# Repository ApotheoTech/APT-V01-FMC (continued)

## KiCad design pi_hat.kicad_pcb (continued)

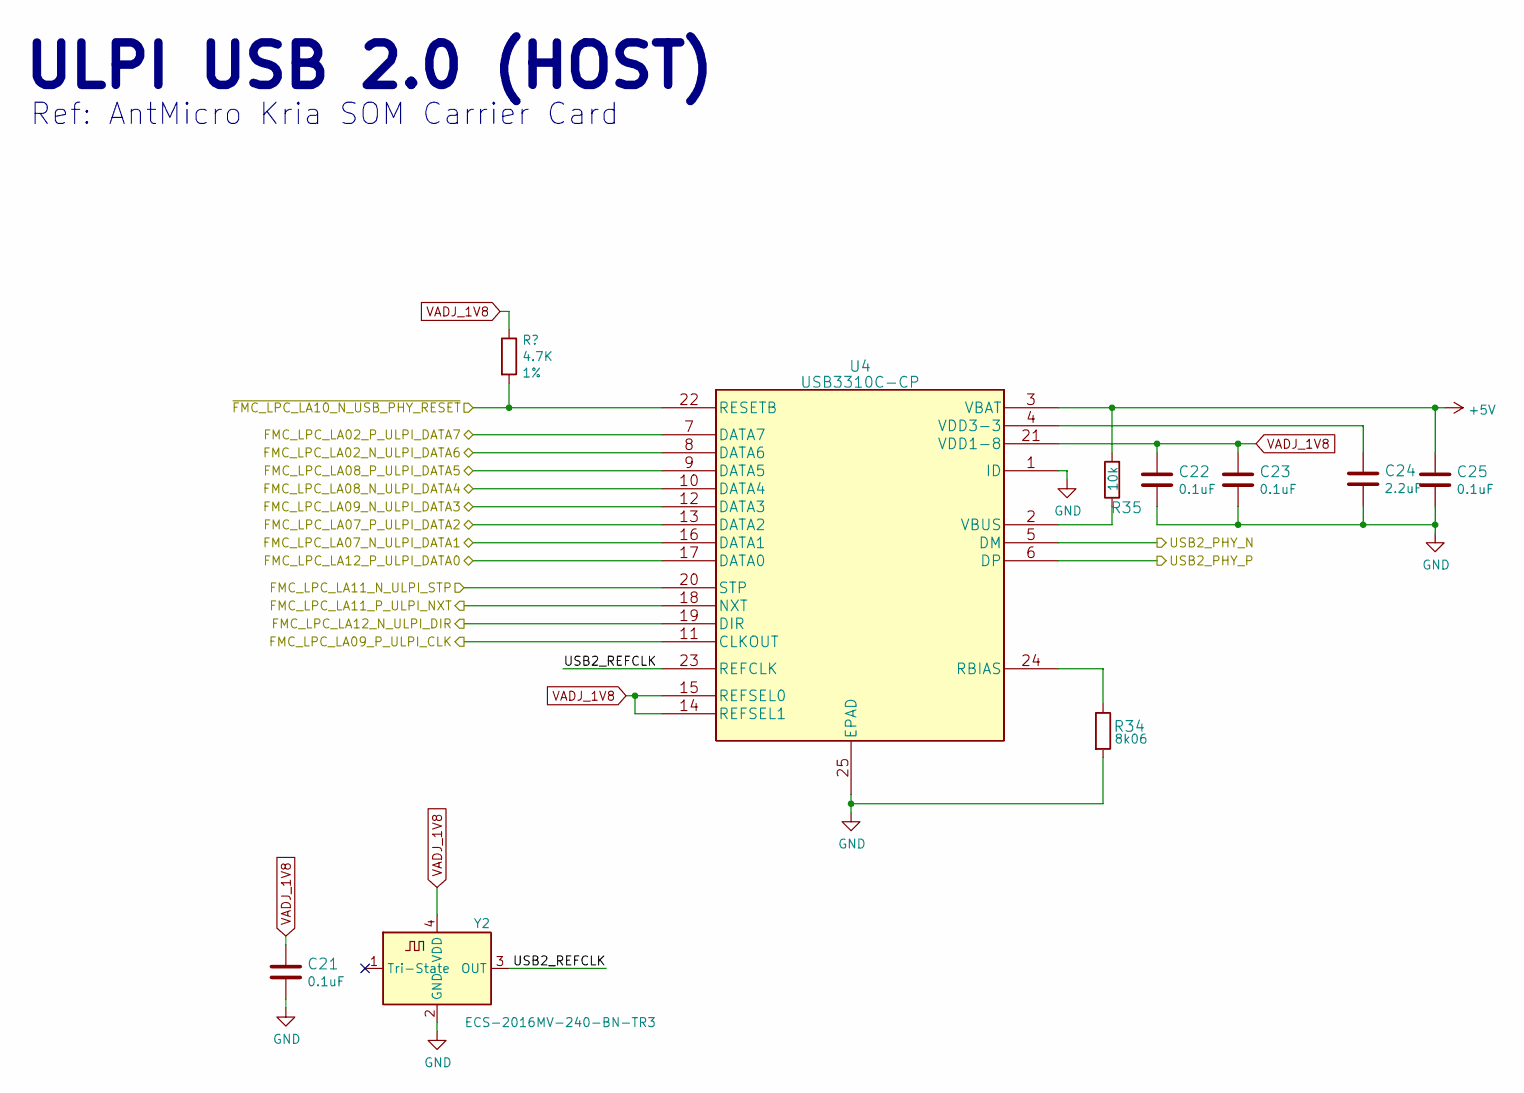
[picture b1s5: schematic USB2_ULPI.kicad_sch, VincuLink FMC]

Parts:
C21, C22, C23, C25: 0.1uF; C_0402_1005Metric; MPN GRM155R61H104KE14D
C24: C_2u2_0402; C_0402_1005Metric; PartNumber C1005X5R1A225K050BC
R33: 4.7K; R_0402_1005Metric; Tolerance 1%; PartNumber CRCW04024K70FKED
R34: 8.06k; R_0402_1005Metric; PartNumber CRCW04028K06FKEDC
R35: R_10k_0402; R_0402_1005Metric; PartNumber CRCW040210K0FKEDHP
U4: USB3310C-CP; Microchip_QFN24_4X4; MPN USB3310C-CP
Y2: ECS-2016MV-240-BN-TR3; ECS-2016MV; MPN ECS-2016MV-240-BN-TR3

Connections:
+5V: C25.1, R35.2, U4.3 (VBAT); also elsewhere on the board
/FMC_Conn/FMC_LPC_LA02_N_ULPI_DATA6: U4.8 (DATA6); also elsewhere on the board
/FMC_Conn/FMC_LPC_LA02_P_ULPI_DATA7: U4.7 (DATA7); also elsewhere on the board
/FMC_Conn/FMC_LPC_LA07_N_ULPI_DATA1: U4.16 (DATA1); also elsewhere on the board
/FMC_Conn/FMC_LPC_LA07_P_ULPI_DATA2: U4.13 (DATA2); also elsewhere on the board
/FMC_Conn/FMC_LPC_LA08_N_ULPI_DATA4: U4.10 (DATA4); also elsewhere on the board
/FMC_Conn/FMC_LPC_LA08_P_ULPI_DATA5: U4.9 (DATA5); also elsewhere on the board
/FMC_Conn/FMC_LPC_LA09_N_ULPI_DATA3: U4.12 (DATA3); also elsewhere on the board
/FMC_Conn/FMC_LPC_LA09_P_ULPI_CLK: U4.11 (CLKOUT); also elsewhere on the board
/FMC_Conn/FMC_LPC_LA11_N_ULPI_STP: U4.20 (STP); also elsewhere on the board
/FMC_Conn/FMC_LPC_LA11_P_ULPI_NXT: U4.18 (NXT); also elsewhere on the board
/FMC_Conn/FMC_LPC_LA12_N_ULPI_DIR: U4.19 (DIR); also elsewhere on the board
/FMC_Conn/FMC_LPC_LA12_P_ULPI_DATA0: U4.17 (DATA0); also elsewhere on the board
/FMC_Conn/~FMC_LPC_LA10_N_USB_PHY_RESET: R33.2, U4.22 (RESETB); also elsewhere on the board
/M_2_KeyE/USB2_PHY_N: U4.5 (DM); also elsewhere on the board
/M_2_KeyE/USB2_PHY_P: U4.6 (DP); also elsewhere on the board
/USB_2_ULPI/USB2_REFCLK: U4.23 (REFCLK), Y2.3 (OUT)
GND: C21.2, C22.2, C23.2, C24.2, C25.2, R34.2, U4.1 (ID), U4.25 (EPAD), Y2.2 (GND); also elsewhere on the board
unnamed: R34.1, U4.24 (RBIAS)
unnamed: R35.1, U4.2 (VBUS)
unnamed: C24.1, U4.4 (VDD3-3)
VADJ_1V8: C21.1, C22.1, C23.1, R33.1, U4.14 (REFSEL1), U4.15 (REFSEL0), U4.21 (VDD1-8), Y2.4 (VDD); also elsewhere on the board

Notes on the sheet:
Ref: AntMicro Kria SOM Carrier Card
ULPI USB 2.0 (HOST)

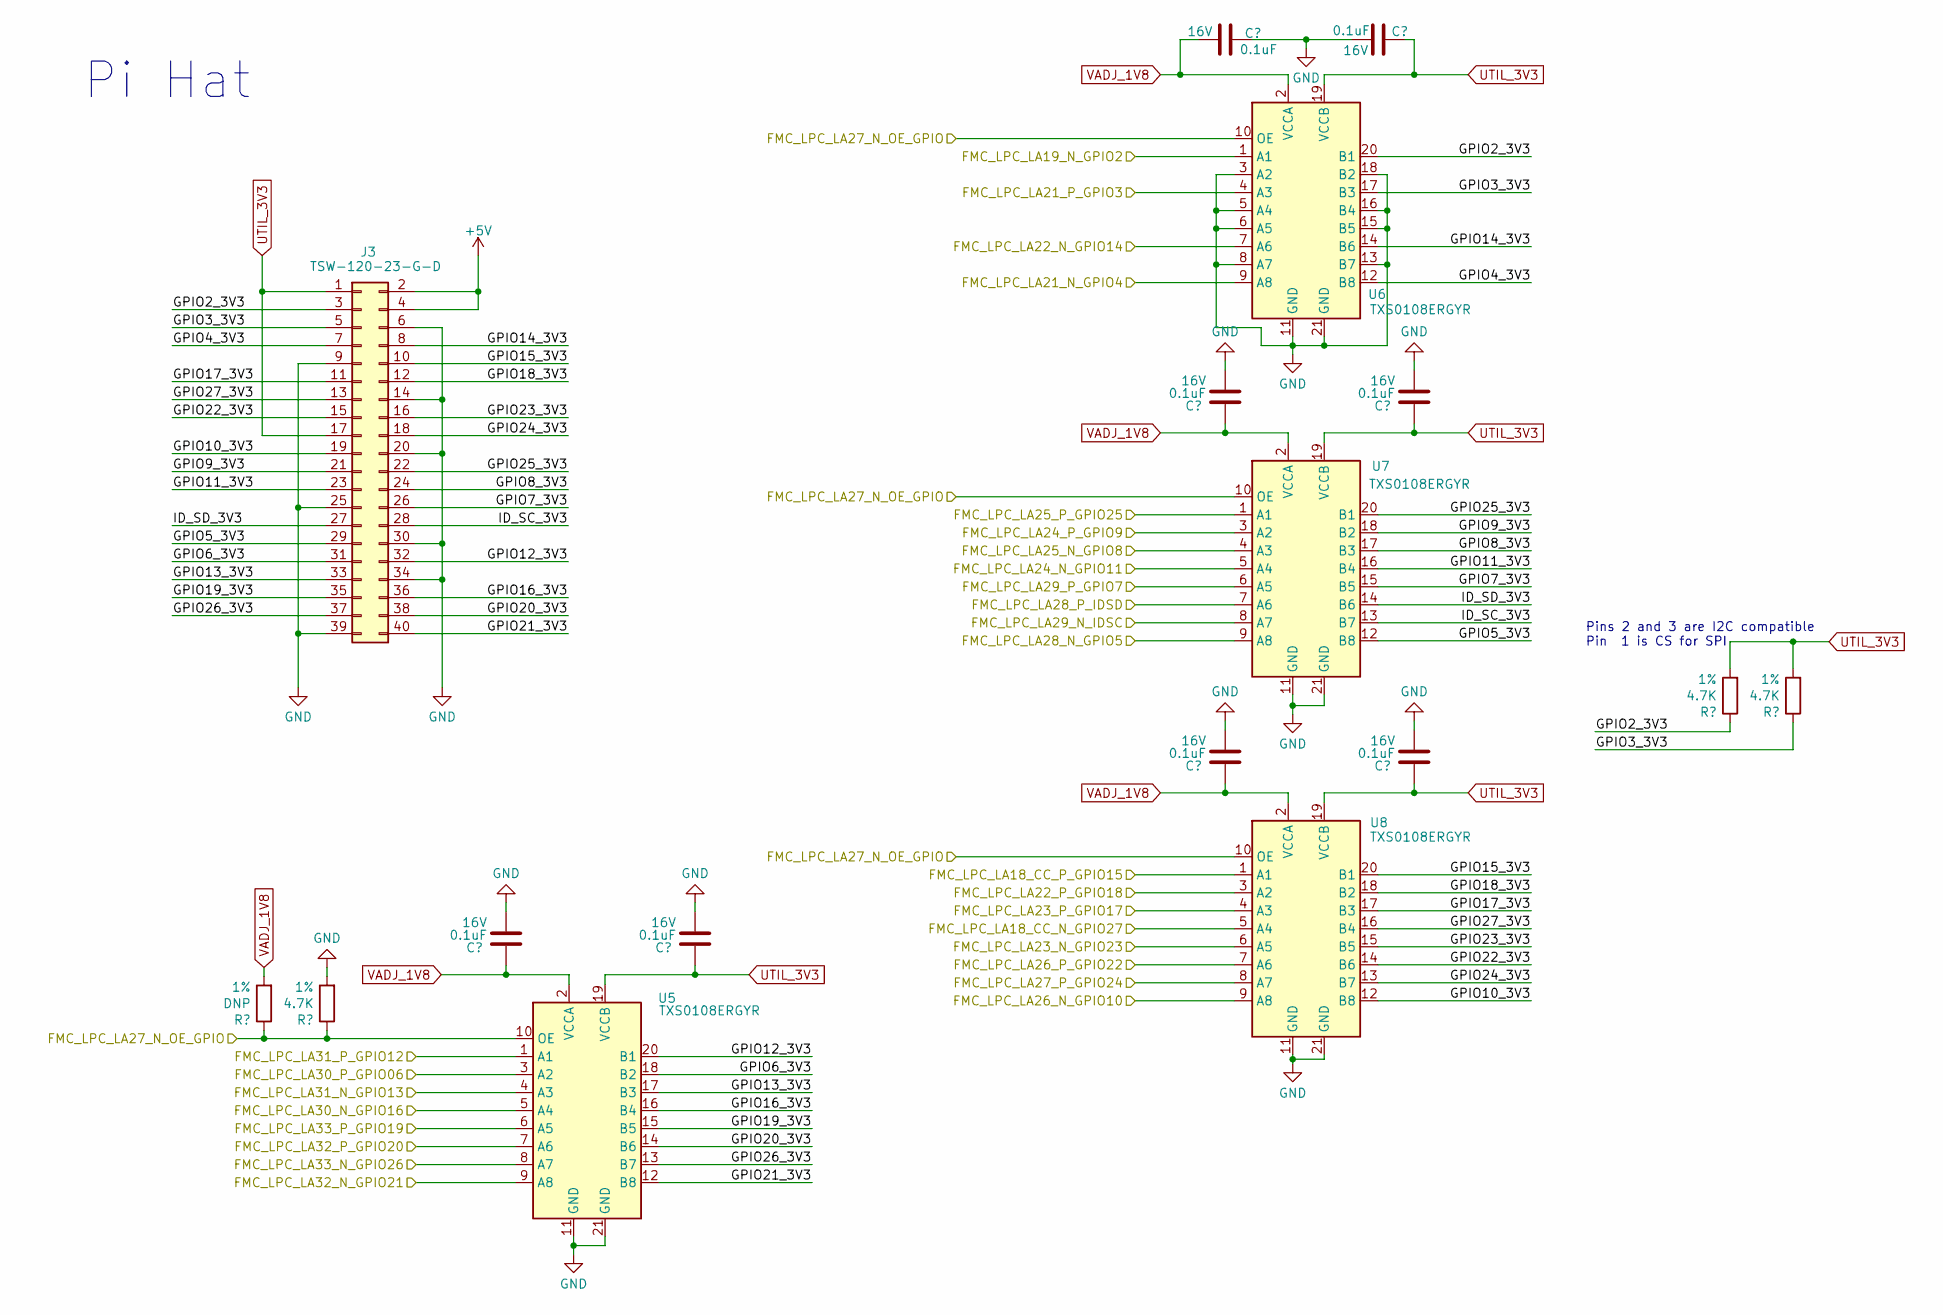
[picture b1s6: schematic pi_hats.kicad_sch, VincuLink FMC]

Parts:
C26, C27, C28, C29, C30, C31, C32, C33: 0.1uF; C_0402_1005Metric; Tolerance +-10%; Voltage 16V; PartNumber EMK105B7104KV-F
J3: TSW-120-23-G-D; PinHeader_2x20_P2.54mm_Vertical
R36: DNP; R_0402_1005Metric; Tolerance 1%; PartNumber CRCW04024K70FKED
R37, R44, R45: 4.7K; R_0402_1005Metric; Tolerance 1%; PartNumber CRCW04024K70FKED
U5, U6, U7, U8: TXS0108ERGYR; TI_VQFN_RGY0020A

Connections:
+5V: J3.2, J3.4; also elsewhere on the board
/FMC_Conn/FMC_LPC_LA18_CC_N_GPIO27: U8.5 (A4); also elsewhere on the board
/FMC_Conn/FMC_LPC_LA18_CC_P_GPIO15: U8.1 (A1); also elsewhere on the board
/FMC_Conn/FMC_LPC_LA19_N_GPIO2: U6.1 (A1); also elsewhere on the board
/FMC_Conn/FMC_LPC_LA21_N_GPIO4: U6.9 (A8); also elsewhere on the board
/FMC_Conn/FMC_LPC_LA21_P_GPIO3: U6.4 (A3); also elsewhere on the board
/FMC_Conn/FMC_LPC_LA22_N_GPIO14: U6.7 (A6); also elsewhere on the board
/FMC_Conn/FMC_LPC_LA22_P_GPIO18: U8.3 (A2); also elsewhere on the board
/FMC_Conn/FMC_LPC_LA23_N_GPIO23: U8.6 (A5); also elsewhere on the board
/FMC_Conn/FMC_LPC_LA23_P_GPIO17: U8.4 (A3); also elsewhere on the board
/FMC_Conn/FMC_LPC_LA24_N_GPIO11: U7.5 (A4); also elsewhere on the board
/FMC_Conn/FMC_LPC_LA24_P_GPIO9: U7.3 (A2); also elsewhere on the board
/FMC_Conn/FMC_LPC_LA25_N_GPIO8: U7.4 (A3); also elsewhere on the board
/FMC_Conn/FMC_LPC_LA25_P_GPIO25: U7.1 (A1); also elsewhere on the board
/FMC_Conn/FMC_LPC_LA26_N_GPIO10: U8.9 (A8); also elsewhere on the board
/FMC_Conn/FMC_LPC_LA26_P_GPIO22: U8.7 (A6); also elsewhere on the board
/FMC_Conn/FMC_LPC_LA27_P_GPIO24: U8.8 (A7); also elsewhere on the board
/FMC_Conn/FMC_LPC_LA28_N_GPIO5: U7.9 (A8); also elsewhere on the board
/FMC_Conn/FMC_LPC_LA28_P_IDSD: U7.7 (A6); also elsewhere on the board
/FMC_Conn/FMC_LPC_LA29_N_IDSC: U7.8 (A7); also elsewhere on the board
/FMC_Conn/FMC_LPC_LA29_P_GPIO7: U7.6 (A5); also elsewhere on the board
/FMC_Conn/FMC_LPC_LA30_N_GPIO16: U5.5 (A4); also elsewhere on the board
/FMC_Conn/FMC_LPC_LA30_P_GPIO06: U5.3 (A2); also elsewhere on the board
/FMC_Conn/FMC_LPC_LA31_N_GPIO13: U5.4 (A3); also elsewhere on the board
/FMC_Conn/FMC_LPC_LA31_P_GPIO12: U5.1 (A1); also elsewhere on the board
/FMC_Conn/FMC_LPC_LA32_N_GPIO21: U5.9 (A8); also elsewhere on the board
/FMC_Conn/FMC_LPC_LA32_P_GPIO20: U5.7 (A6); also elsewhere on the board
/FMC_Conn/FMC_LPC_LA33_N_GPIO26: U5.8 (A7); also elsewhere on the board
/FMC_Conn/FMC_LPC_LA33_P_GPIO19: U5.6 (A5); also elsewhere on the board
/pi_hats/GPIO4_3V3: J3.7, U6.12 (B8)
/pi_hats/GPIO5_3V3: J3.29, U7.12 (B8)
/pi_hats/GPIO6_3V3: J3.31, U5.18 (B2)
/pi_hats/GPIO7_3V3: J3.26, U7.15 (B5)
/pi_hats/GPIO8_3V3: J3.24, U7.17 (B3)
/pi_hats/GPIO9_3V3: J3.21, U7.18 (B2)
/pi_hats/GPIO10_3V3: J3.19, U8.12 (B8)
/pi_hats/GPIO11_3V3: J3.23, U7.16 (B4)
/pi_hats/GPIO12_3V3: J3.32, U5.20 (B1)
/pi_hats/GPIO13_3V3: J3.33, U5.17 (B3)
/pi_hats/GPIO14_3V3: J3.8, U6.14 (B6)
/pi_hats/GPIO15_3V3: J3.10, U8.20 (B1)
/pi_hats/GPIO16_3V3: J3.36, U5.16 (B4)
/pi_hats/GPIO17_3V3: J3.11, U8.17 (B3)
/pi_hats/GPIO18_3V3: J3.12, U8.18 (B2)
/pi_hats/GPIO19_3V3: J3.35, U5.15 (B5)
/pi_hats/GPIO20_3V3: J3.38, U5.14 (B6)
/pi_hats/GPIO21_3V3: J3.40, U5.12 (B8)
/pi_hats/GPIO22_3V3: J3.15, U8.14 (B6)
/pi_hats/GPIO23_3V3: J3.16, U8.15 (B5)
/pi_hats/GPIO24_3V3: J3.18, U8.13 (B7)
/pi_hats/GPIO25_3V3: J3.22, U7.20 (B1)
/pi_hats/GPIO26_3V3: J3.37, U5.13 (B7)
/pi_hats/GPIO27_3V3: J3.13, U8.16 (B4)
/pi_hats/ID_SC_3V3: J3.28, U7.13 (B7)
/pi_hats/ID_SD_3V3: J3.27, U7.14 (B6)
GND: C26.1, C27.1, C28.2, C29.1, C30.1, C31.1, C32.1, C33.1, J3.6, J3.9, J3.14, J3.20, J3.25, J3.30, J3.34, J3.39, R37.2, U5.11 (GND), U5.21 (GND), U6.3 (A2), U6.5 (A4), U6.6 (A5), U6.8 (A7), U6.11 (GND), U6.13 (B7), U6.15 (B5), U6.16 (B4), U6.18 (B2), U6.21 (GND), U7.11 (GND), U7.21 (GND), U8.11 (GND), U8.21 (GND); also elsewhere on the board
UTIL_3V3: C27.2, C31.2, C32.2, C33.2, J3.1, J3.17, R44.2, R45.2, U5.19 (VCCB), U6.19 (VCCB), U7.19 (VCCB), U8.19 (VCCB); also elsewhere on the board
VADJ_1V8: C26.2, C28.1, C29.2, C30.2, R36.2, U5.2 (VCCA), U6.2 (VCCA), U7.2 (VCCA), U8.2 (VCCA); also elsewhere on the board

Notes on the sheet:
Pins 2 and 3 are I2C compatible Pin 1 is CS for SPI
Pi Hat

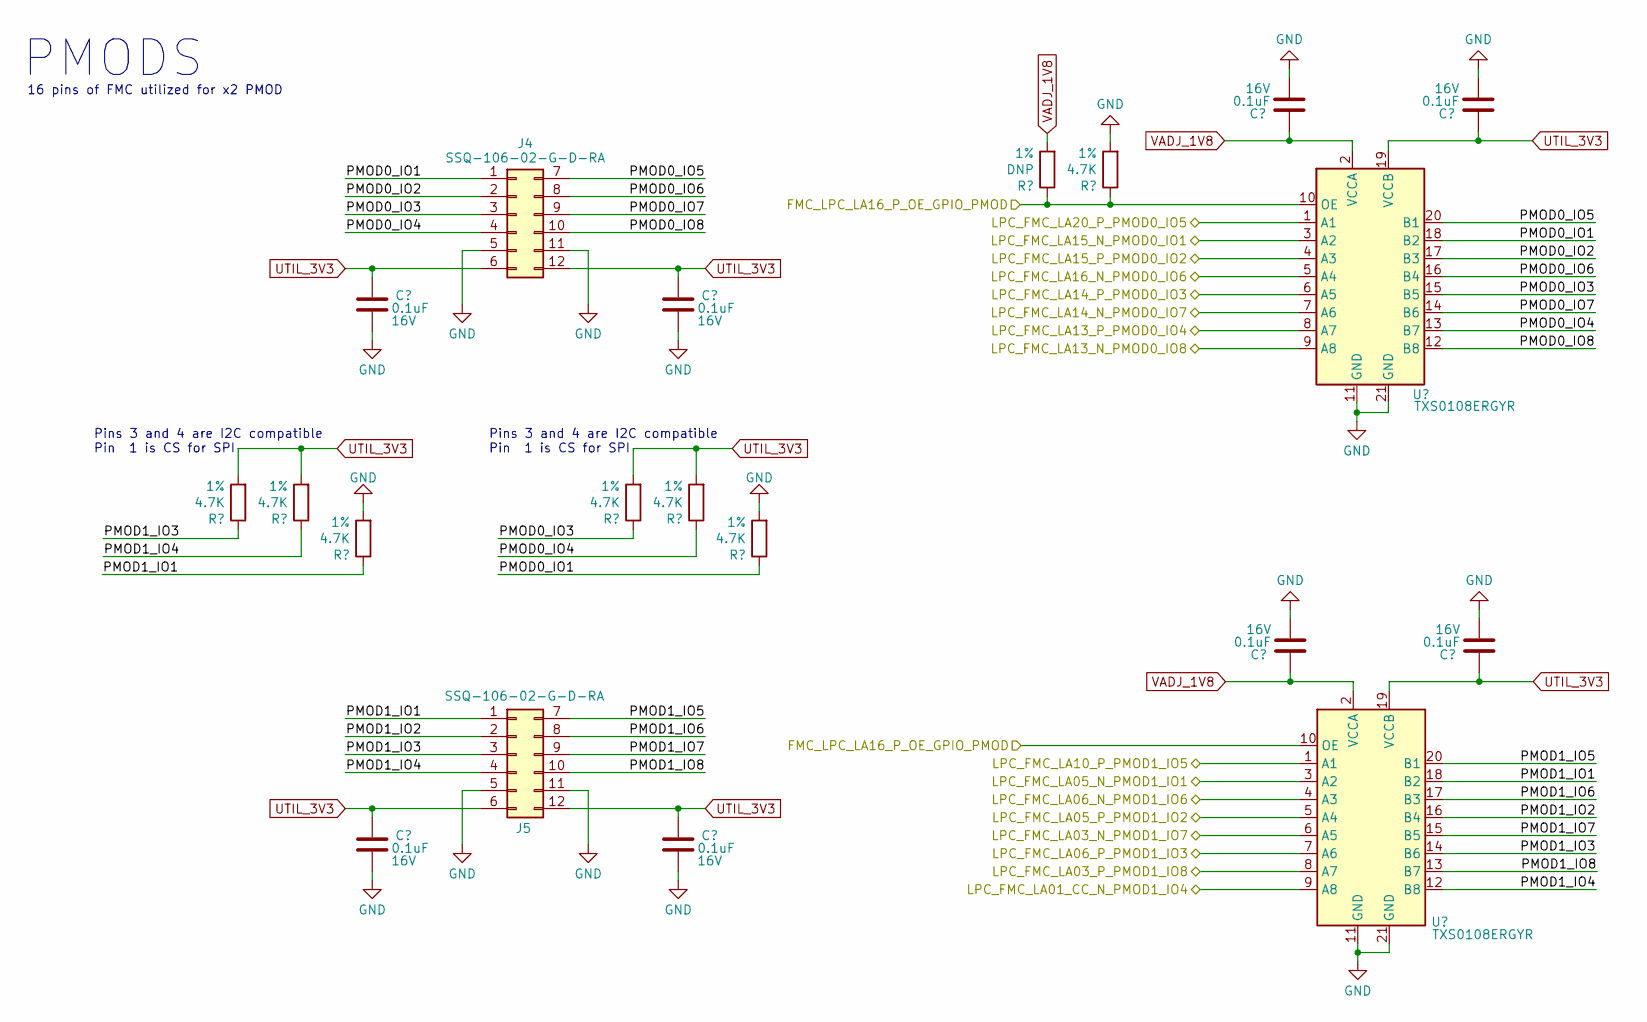
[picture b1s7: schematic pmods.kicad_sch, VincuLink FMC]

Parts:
C34, C35, C36, C37, C38, C39, C40, C41: 0.1uF; C_0402_1005Metric; Tolerance +-10%; Voltage 16V; PartNumber EMK105B7104KV-F
J4, J5: SSQ-106-02-G-D-RA; PMOD
R44, R45, R46, R47, R48, R49, R52: 4.7K; R_0402_1005Metric; Tolerance 1%; PartNumber CRCW04024K70FKED
R50: DNP; R_0402_1005Metric; Tolerance 1%; PartNumber CRCW04024K70FKED
U9, U10: TXS0108ERGYR; TI_VQFN_RGY0020A

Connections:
/FMC_Conn/FMC_LPC_LA01_CC_N_PMOD1_IO4: U10.9 (A8); also elsewhere on the board
/FMC_Conn/FMC_LPC_LA03_N_PMOD1_IO7: U10.6 (A5); also elsewhere on the board
/FMC_Conn/FMC_LPC_LA03_P_PMOD1_IO8: U10.8 (A7); also elsewhere on the board
/FMC_Conn/FMC_LPC_LA05_N_PMOD1_IO1: U10.3 (A2); also elsewhere on the board
/FMC_Conn/FMC_LPC_LA05_P_PMOD1_IO2: U10.5 (A4); also elsewhere on the board
/FMC_Conn/FMC_LPC_LA06_N_PMOD1_IO6: U10.4 (A3); also elsewhere on the board
/FMC_Conn/FMC_LPC_LA06_P_PMOD1_IO3: U10.7 (A6); also elsewhere on the board
/FMC_Conn/FMC_LPC_LA10_P_PMOD1_IO5: U10.1 (A1); also elsewhere on the board
/FMC_Conn/FMC_LPC_LA13_N_PMOD0_IO8: U9.9 (A8); also elsewhere on the board
/FMC_Conn/FMC_LPC_LA13_P_PMOD0_IO4: U9.8 (A7); also elsewhere on the board
/FMC_Conn/FMC_LPC_LA14_N_PMOD0_IO7: U9.7 (A6); also elsewhere on the board
/FMC_Conn/FMC_LPC_LA14_P_PMOD0_IO3: U9.6 (A5); also elsewhere on the board
/FMC_Conn/FMC_LPC_LA15_N_PMOD0_IO1: U9.3 (A2); also elsewhere on the board
/FMC_Conn/FMC_LPC_LA15_P_PMOD0_IO2: U9.4 (A3); also elsewhere on the board
/FMC_Conn/FMC_LPC_LA16_N_PMOD0_IO6: U9.5 (A4); also elsewhere on the board
/FMC_Conn/FMC_LPC_LA16_P_OE_GPIO_PMOD: R50.1, R52.1, U9.10 (OE), U10.10 (OE); also elsewhere on the board
/FMC_Conn/FMC_LPC_LA20_P_PMO0_IO5: U9.1 (A1); also elsewhere on the board
/PMODS/PMOD0_IO1: J4.1, R49.1, U9.18 (B2)
/PMODS/PMOD0_IO2: J4.2, U9.17 (B3)
/PMODS/PMOD0_IO3: J4.3, R47.1, U9.15 (B5)
/PMODS/PMOD0_IO4: J4.4, R48.1, U9.13 (B7)
/PMODS/PMOD0_IO5: J4.7, U9.20 (B1)
/PMODS/PMOD0_IO6: J4.8, U9.16 (B4)
/PMODS/PMOD0_IO7: J4.9, U9.14 (B6)
/PMODS/PMOD0_IO8: J4.10, U9.12 (B8)
/PMODS/PMOD1_IO1: J5.1, R46.1, U10.18 (B2)
/PMODS/PMOD1_IO2: J5.2, U10.16 (B4)
/PMODS/PMOD1_IO5: J5.7, U10.20 (B1)
/PMODS/PMOD1_IO6: J5.8, U10.17 (B3)
/PMODS/PMOD1_IO7: J5.9, U10.15 (B5)
/PMODS/PMOD1_IO8: J5.10, U10.13 (B7)
GND: C34.1, C35.1, C36.1, C37.1, C38.1, C39.1, C40.1, C41.1, J4.5, J4.11, J5.5, J5.11, R46.2, R49.2, R52.2, U9.11 (GND), U9.21 (GND), U10.11 (GND), U10.21 (GND); also elsewhere on the board
UTIL_3V3: C34.2, C35.2, C36.2, C37.2, C40.2, C41.2, J4.6, J4.12, J5.6, J5.12, R44.2, R45.2, R47.2, R48.2, U9.19 (VCCB), U10.19 (VCCB); also elsewhere on the board
VADJ_1V8: C38.2, C39.2, R50.2, U9.2 (VCCA), U10.2 (VCCA); also elsewhere on the board

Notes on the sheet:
Pins 3 and 4 are I2C compatible Pin 1 is CS for SPI
PMODS
16 pins of FMC utilized for x2 PMOD

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
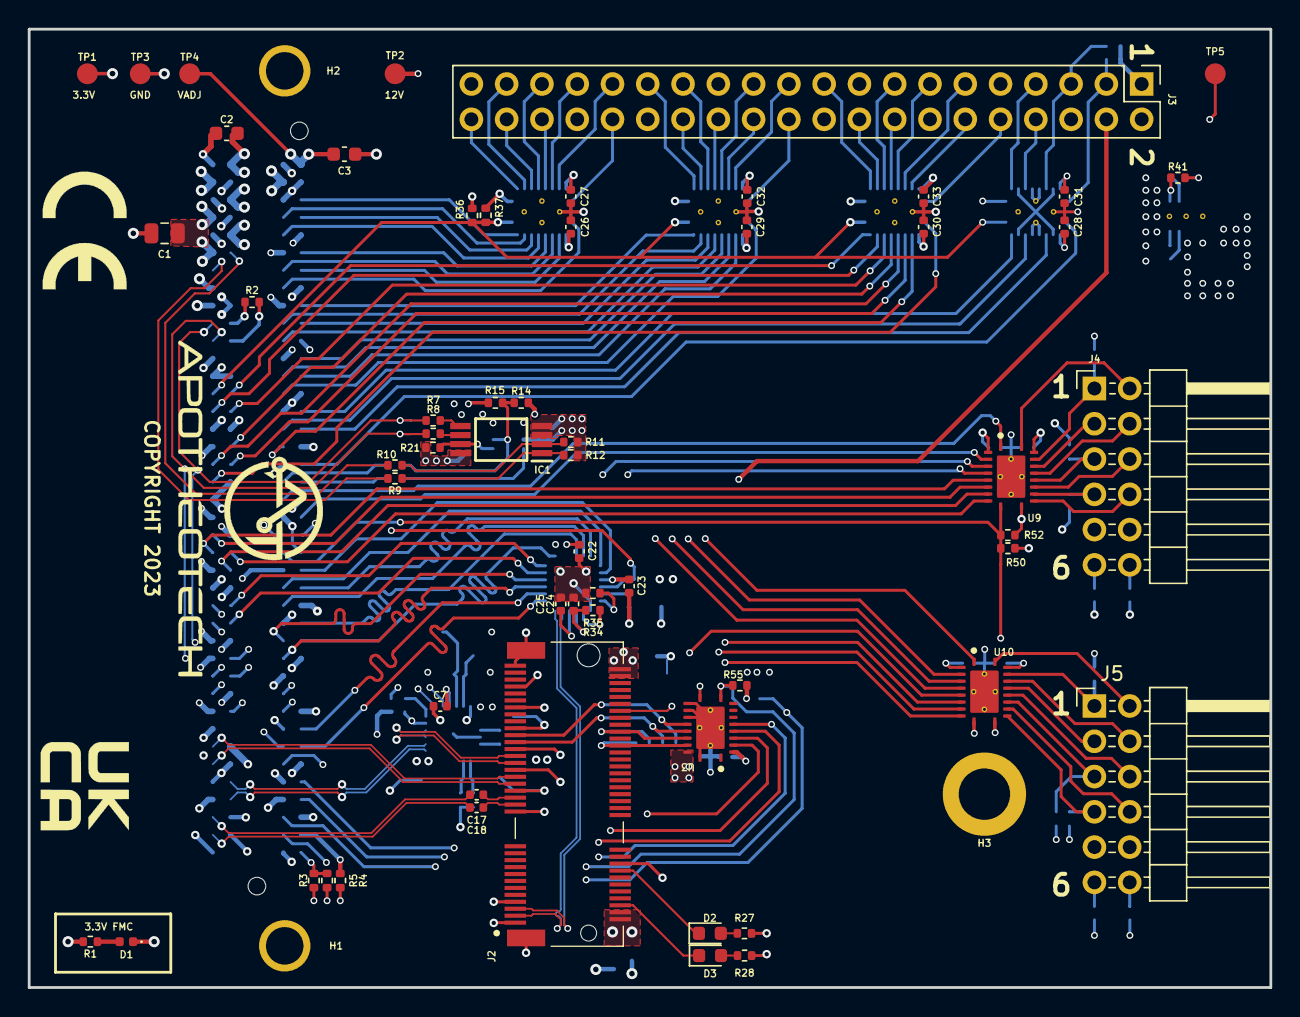
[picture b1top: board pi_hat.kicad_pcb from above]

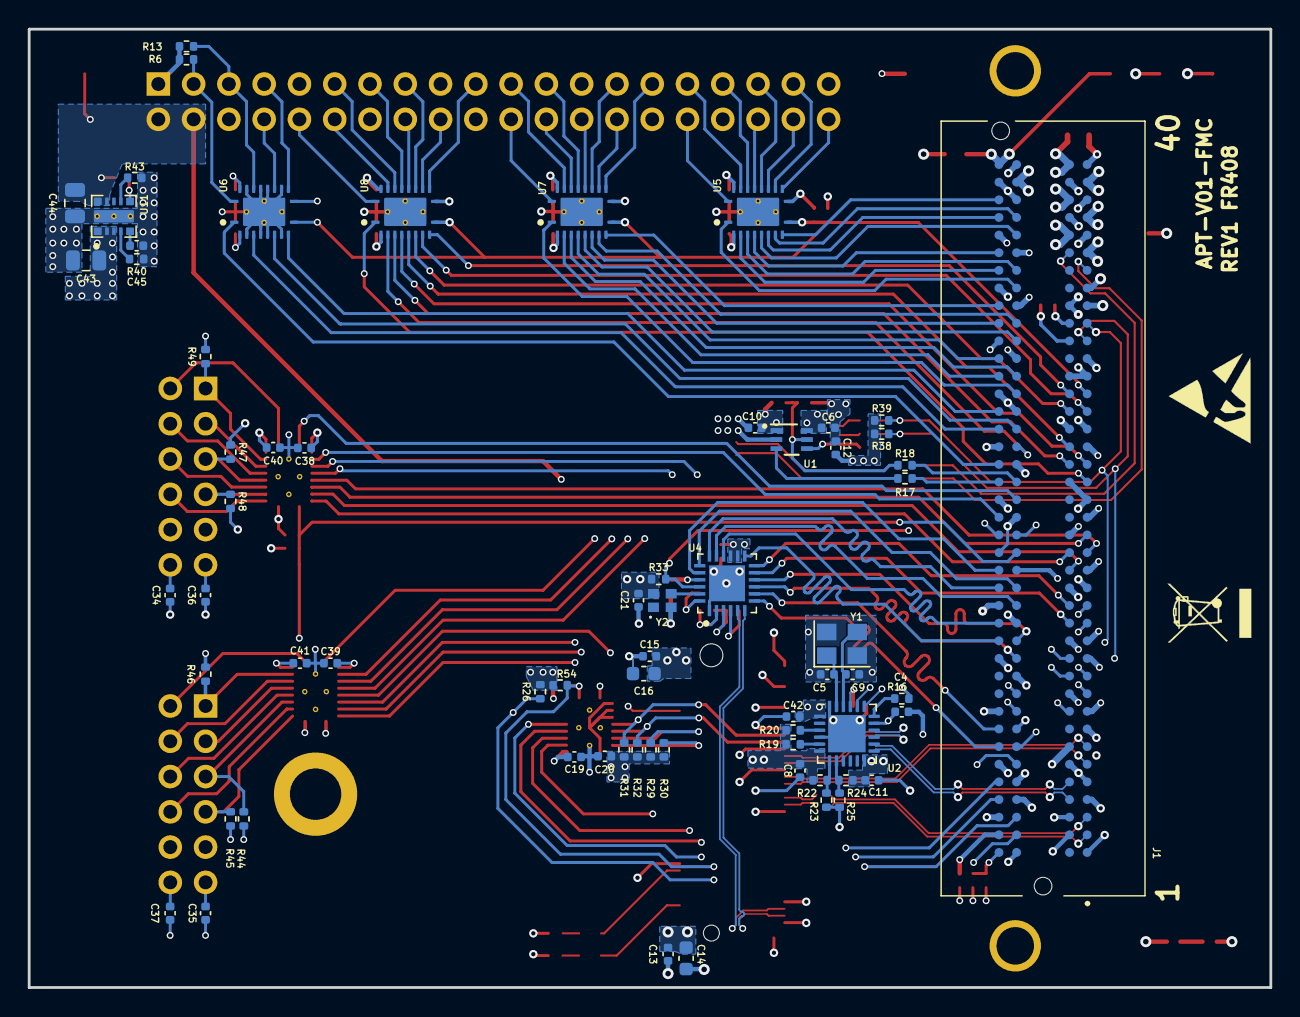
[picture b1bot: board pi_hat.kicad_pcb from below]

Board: 6 copper layers, 89.4 x 69.0 mm, 132 parts (68 on the bottom side), 168 nets.

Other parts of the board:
R6, R13, R55: 4.7K; R_0402_1005Metric
R54: DNP; R_0402_1005Metric

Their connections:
GND: R55.2; also elsewhere on the board
UTIL_3V3: R6.2, R13.2; also elsewhere on the board
VADJ_1V8: R54.2; also elsewhere on the board

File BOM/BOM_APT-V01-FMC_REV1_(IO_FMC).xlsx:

Ref | Qnty | Value | Part Number | Alternate
C1 | 1 | 10uF | GRM21BR61E106MA73L
C2, C3 | 2 | 10uF | GRM188R61A106KE69D | 0603ZD106KAT2A
C4, C6, C7, C8, C10, C11, C12, C19, C20, C26, C27, C28, C29, C30, C31, C32, C33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 | 26 | 0.1uF | EMK105B7104KV-F
C5, C9 | 2 | 14pF | 04025U140FAT2A
C13, C15 | 2 | 1uF | C0402C105Z9VACTU
C14, C16 | 2 | 10uF | 06036D106MAT2A
C17, C18 | 2 | 0.1uF | C1005X5R0J104K050BA
C21, C22, C23, C25 | 4 | 0.1uF | EMK105B7104KV-F
C24 | 1 | C_2u2_0402 | C1005X5R1A225K050BC
C43, C44 | 2 | 22uF | C2012X5R1V226M125AC
C45 | 1 | 1nF | GRM155R61A102KA01D
D1 | 1 | GRN LED | 5988A80107F
D2, D3 | 2 | APT1608SGC | APT1608SGC
H3 | 1 | 9774015151R | 9774015151R
IC1 | 1 | M24C64-DRDW8TP_K | M24C64-DRDW8TP_K
J1 | 1 | ASP-134604-01 | ASP-134604-01
J2 | 1 | 2199119-4 | 2199119-4
J3 | 1 | TSW-120-23-G-D | TSW-120-23-G-D
J4, J5 | 2 | SSQ-106-02-G-D-RA | SSQ-106-02-G-D-RA
R1, R6, R13, R15, R16, R19, R20, R21, R22, R23, R24, R25, R33, R37, R38, R39, R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 | 24 | 4.7K | CRCW04024K70FKED
R2, R4, R5, R7, R8, R9, R10, R17, R18 | 9 | 0 | CRCW04020000Z0EDHP
R3, R11, R12 | 3 | DNP | CRCW04020000Z0EDHP
R14, R36, R50, R54 | 4 | DNP | CRCW04024K70FKED
R26, R29, R30, R31, R32 | 5 | 10K | ERJ-2RKF1002X
R27, R28 | 2 | 220 | RC0402JR-07220RL
R34 | 1 | 8.06k | CRCW04028K06FKEDC
R35 | 1 | R_10k_0402 | CRCW040210K0FKEDHP
R40 | 1 | 40.2k | ERJ-2RKF4022X
R41 | 1 | 100k | CRCW0402100KFKEDHP
R43 | 1 | 76.8k | CRCW040276K8FKED
U1 | 1 | SN74AXC1T45DCKR | SN74AXC1T45DCKR
U2 | 1 | Si52131-A11A | Si52131-A11A
U3, U5, U6, U7, U8, U9, U10 | 7 | TXS0108EPW | TXS0108EPW
U4 | 1 | USB3310C-CP | USB3310C-CP
U11 | 1 | TPSM82902SISR | TPSM82902SISR
Y1 | 1 | 830105863709 | 830105863709
Y2 | 1 | ECS-2016MV-240-BN-TR3 | ECS-2016MV-240-BN-TR3

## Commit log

2023-12-22 init commit
2023-12-22 add images to readme
